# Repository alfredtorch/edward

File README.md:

Edward is an innovative solution that synergizes citizen science with urban farming, utilizing an advanced aquaponic system to address environmental challenges. Edward aims to produce sustainable food sources while fostering community involvement and contributing to a healthier, more sustainable urban environment.

Designed as an expansive urban farming laboratory, Edward initially focuses on aquaponics. This highly efficient farming method is capable of producing local food with minimal resource impact and effort. By transforming existing water bodies, such as ponds or basins, into productive food sources, Edward epitomizes the principles of the circular economy.

Key Features
- Smart Garden Community: Build your self-sufficient technology platform and transform public spaces into urban farming areas.
- Citizen Science: Share information and engage in community-driven research.
- Open Source: Driven by the community, promoting collaboration and innovation.
- Modular Design: Based on the principles of the circular economy, allowing adaptability and scalability.

> ## Software Development Needed
> Please visit the [Software Specification Sheet](SoftwareSpecificationSheetM2.md) if you would like to collaborate and help to develop Edward.
> ## On-Going Documentation
> Different sections in this repository needs to verified. Please feel free to submit corrections, if you would like to collaborate and help to develop Edward.

# Growing Lab & Sharing Knowledge
Edward fosters continuous improvement through community involvement at multiple levels. Individuals manage local stations, benefit from fresh food, and participate in testing new biological scenarios. This approach enriches community knowledge and enhances the numerical model.

The Sustainable Food Cycle and Optimization Biological Cycle are central to Edward's innovative approach. The Sustainable Food Cycle focuses on creating a cradle-to-cradle system where organic waste is transformed into bio converters and natural bio cycles, producing organic food for fish and yielding fresh vegetables. This cycle epitomizes resource efficiency and sustainability. Meanwhile, the Optimization Biological Cycle leverages citizen science and advanced technologies like machine learning and autonomous control to refine and enhance farming practices. Through community-driven research, scenario experimentation, and gamification, this cycle ensures continuous improvement and optimization of the entire system.

## Sharing Knowledge
For individuals, Edward offers a novel way to connect with nature and their community. Members assume shared responsibility for their plants and fish, gaining knowledge and forming new connections, both digitally and in person. This hands-on experience not only yields healthy food but also underlines a Return on Research (RoR) approach, valuing the knowledge gained from community-led research and innovation.

Key Features
* Citizen-Operated Stations: Gather observations for new biological scenarios like light conditions or tidal cycles.
* Mobile App Support: Easy sharing of observations with scientists, encouraging dynamic information exchange.
* Participative and Gamified Approach: Encourages dialogue, sharing through text and images, and collective data contribution.
* AI-Driven Insights: Data from multiple stations feed into AI models for valuable insights into small-scale and industrial agricultural practices, such as pisciculture.

## Research Project 1 : Water Cooled LEDs

Improve the maintenance cost and efficiency with water-cooled LEDs for grow lights. This study focuses on the efficient thermal management of the grow light. Optimal cooling will provide long-term stable light characteristics and increase lifespan. Additionally, the possible waste heat can be used to heat the fish tank.

## Phases
1. **Design Possibilities:** Explore various design possibilities such as heat sinks, LED holders, and more.
2. **Check Safety Concerns:** Address safety concerns including risks of electrocution, fire hazards, and appropriate light levels.
3. **Regulate Water Pump and Light Intensity:** Control the water pump and adjust light intensity based on a state machine and scheduling.
4. **Measure Light Quality:** Assess light quality by measuring energy, wavelengths, and consumption over time.

## Development Project 1 : Move away from Home Assistant

The current prototype system is powered by Home Assistant with ESPHome running on a local Raspberry Pi. This setup was great for quickly prototyping a proof of concept. However, the main challenges faced by the current system are:
- It is not a standalone system (requires both Raspberry Pi and Station Controller).
- There is no option for easy remote monitoring of the system (NAT, DNS, Public IP).
- Missing control options (regular self-calibration, failsafe mode).

<p align="center>
  >
</p>

# Files & Folders
The project is currently mainly organised in this respository.
All shared by Licence... 
## [Hardware](Hardware.md)
## [Hardware PCB Repo](/Hardware/)
## [Components](Components.md)
## [Software YAML Repo](/Software/)
## [Software Devlopement Specification Sheet](SoftwareSpecificationSheetM2.md)
## [Discord Server](https://discord.gg/AFunXj2wjE)
## [HackADay.io Project](https://hackaday.io/project/197025-edwardfarm)

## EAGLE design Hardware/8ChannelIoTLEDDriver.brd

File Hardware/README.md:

| Filename | Notes |
| --- | --- |
FishTankControllerV2 | Control the Greenhouse & Fish Tank with safe DC motors |
GreenHouseControllerV2 | Control the Greenhouse & Fish Tank with with powerful AC motors |
IoTSSensorBoardV2 | Measure Heatsink Temperature LM75B or TMP1075 |
PowerMosfetGSVINRailV1 | Control 4 DC Load Module with GreenHouseControllerV2 |
PowerMosfetsSGVINRailV1 | Control 4 DC Load Modulel Module with GreenHouseControllerV2 |
Relay4ChannelBoard | Control 230V Relay 4Channel Module with GreenHouseControllerV2 |
SSR4ChannelBoard | Control 230V SSR 4Channel Module with GreenHouseControllerV2 |

<p align="center">

<br>
8 Channel Rebel - 8ChannelRebelSSR_v5
<br>

<br>
Helios - 8ChannelIoTLEDDriver
<br>

<br>
Green House - GreenHouseControllerV2
<br>

<br>
FishTankControllerV2
<br>

<br>
Relay4ChannelBoard - Control 230V Relay 4Channel Module with Green-House
<br>

<br>
SSR4ChannelBoard - Control 230V SSR 4Channel Module with Green-House
<br>

<br>
PowerMosfetGSVINRailV1
<br>

PowerMosfetSGVINRailV1
<br>
</p>

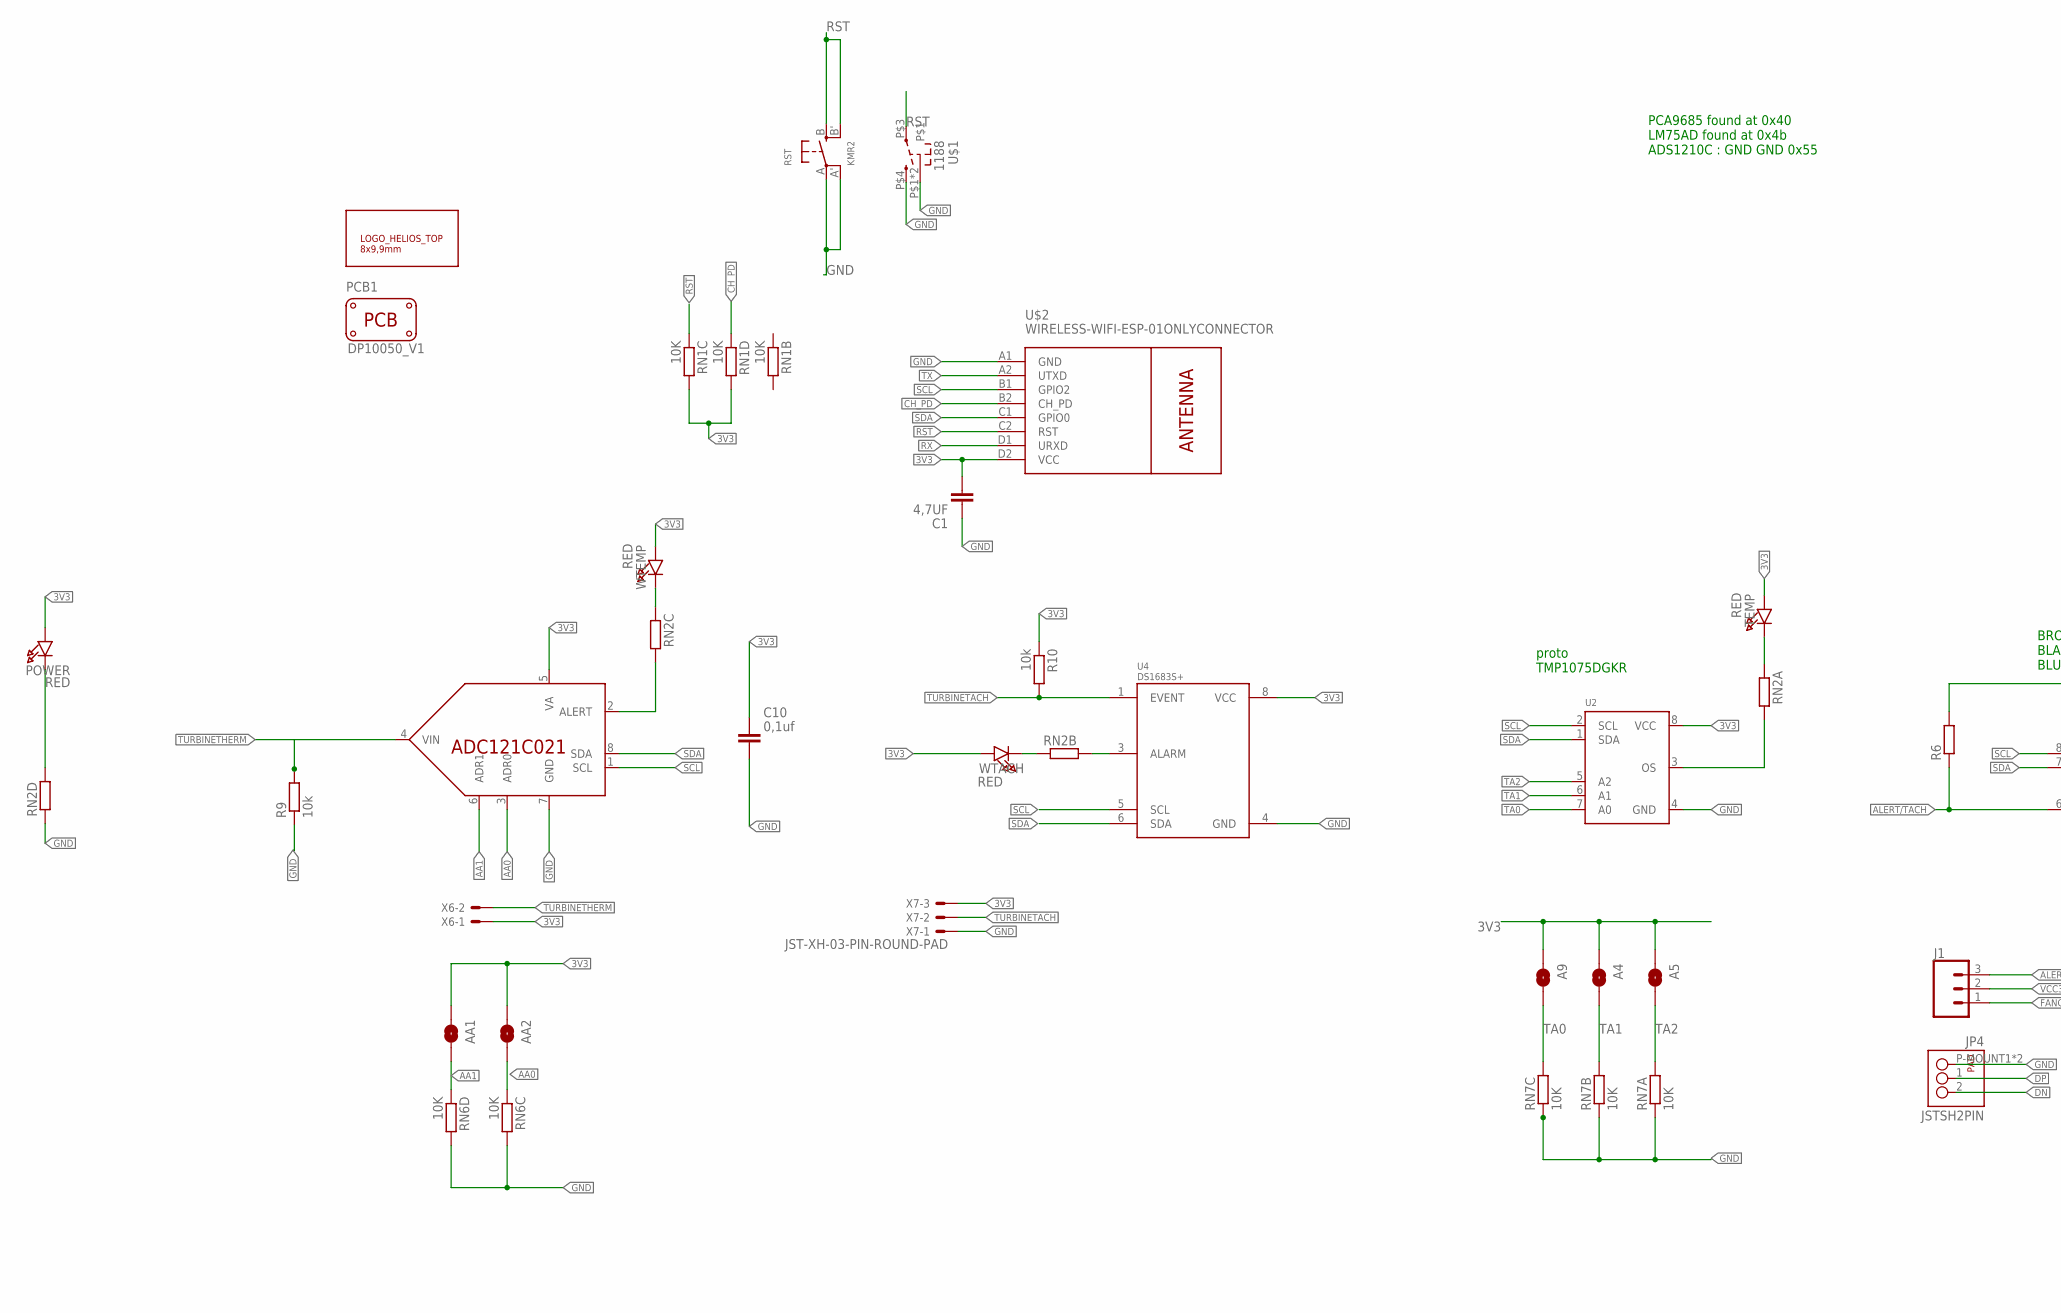
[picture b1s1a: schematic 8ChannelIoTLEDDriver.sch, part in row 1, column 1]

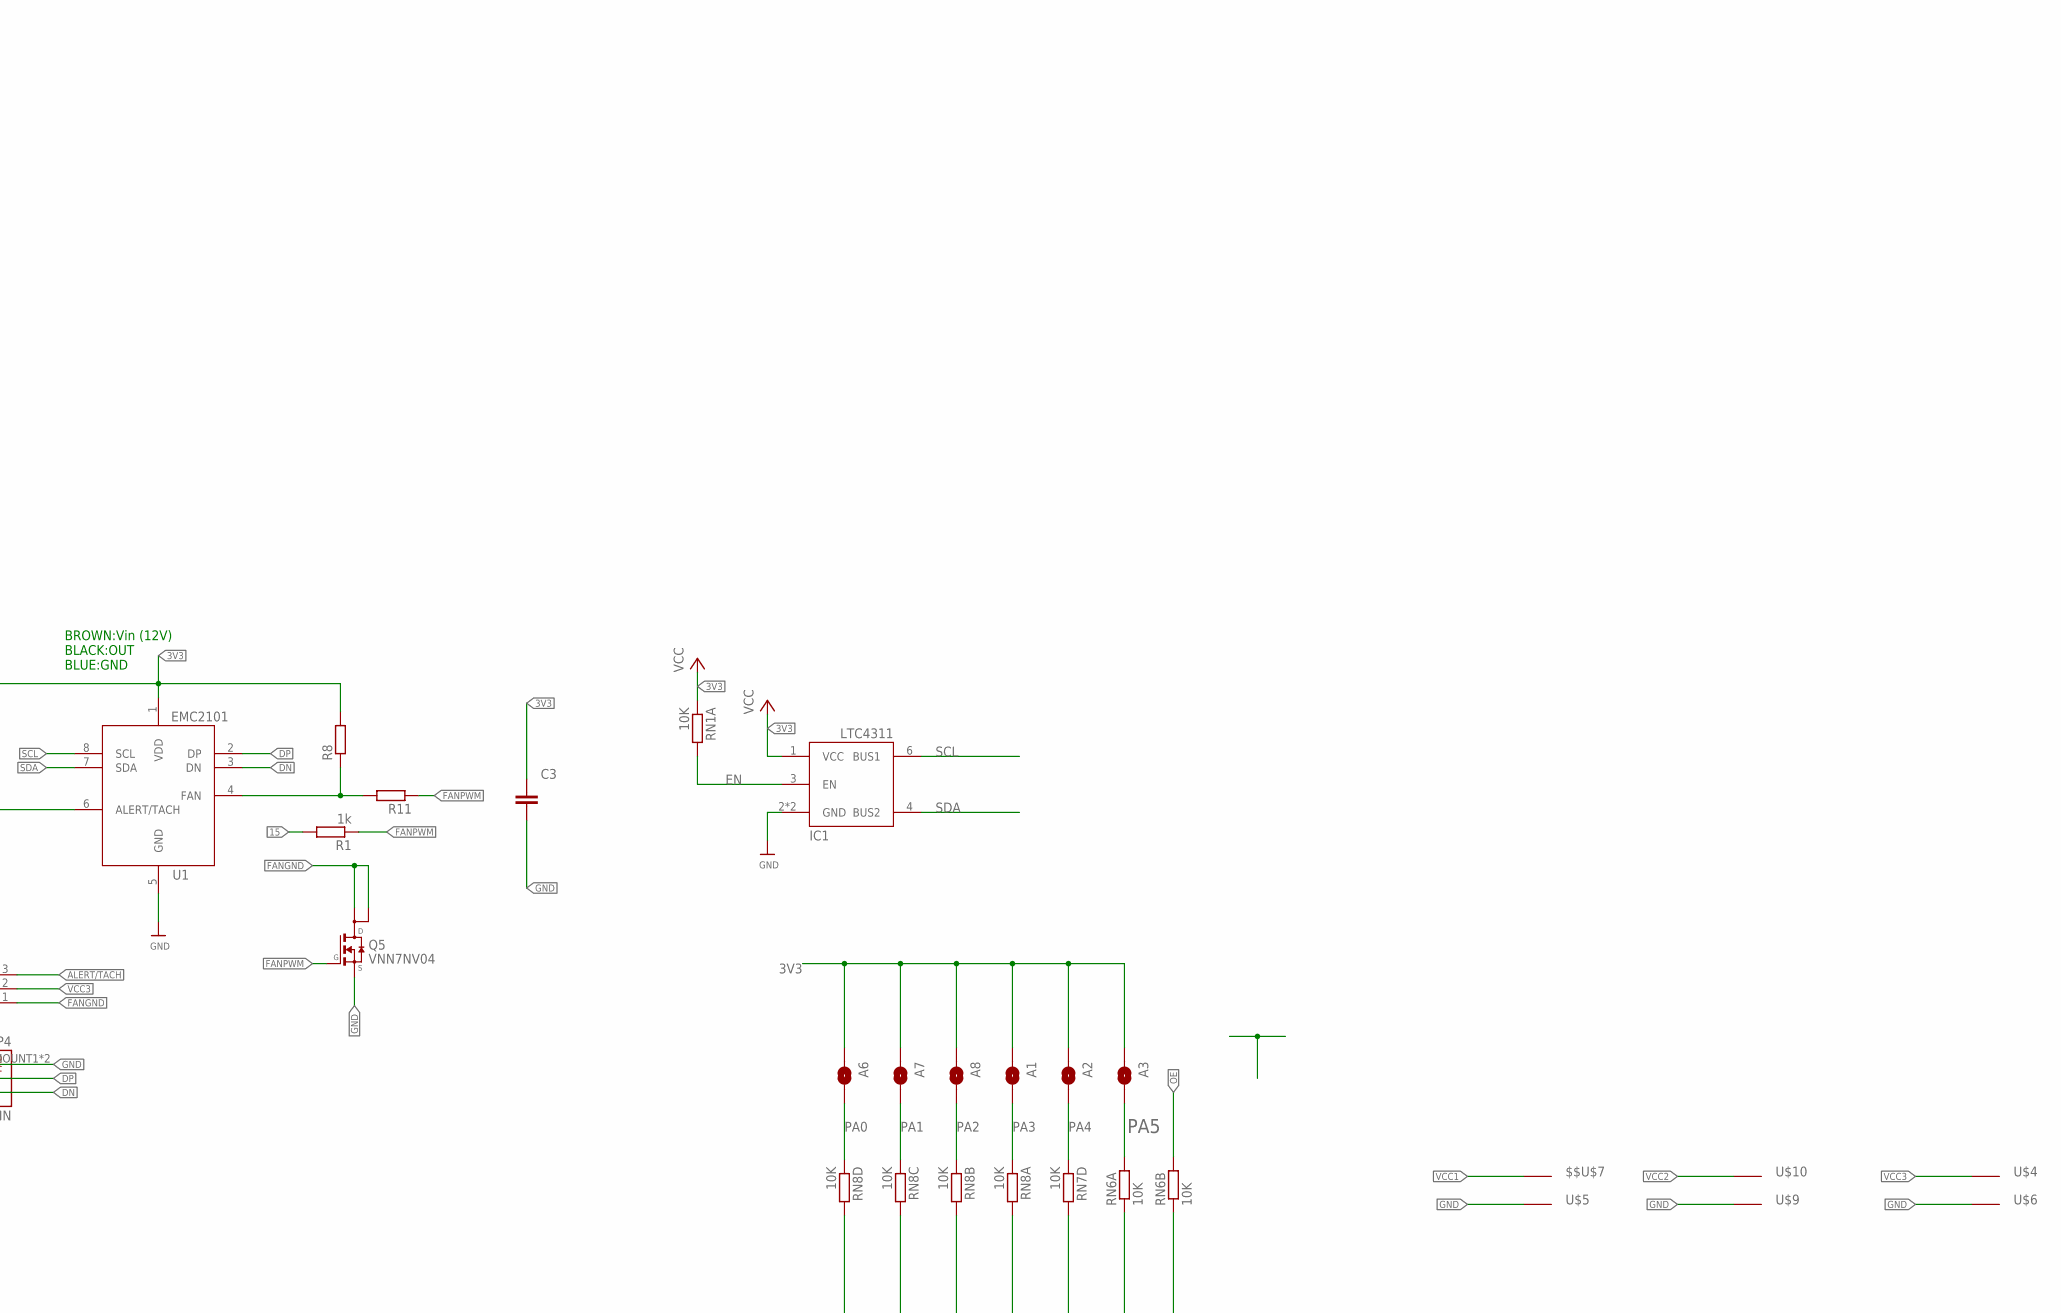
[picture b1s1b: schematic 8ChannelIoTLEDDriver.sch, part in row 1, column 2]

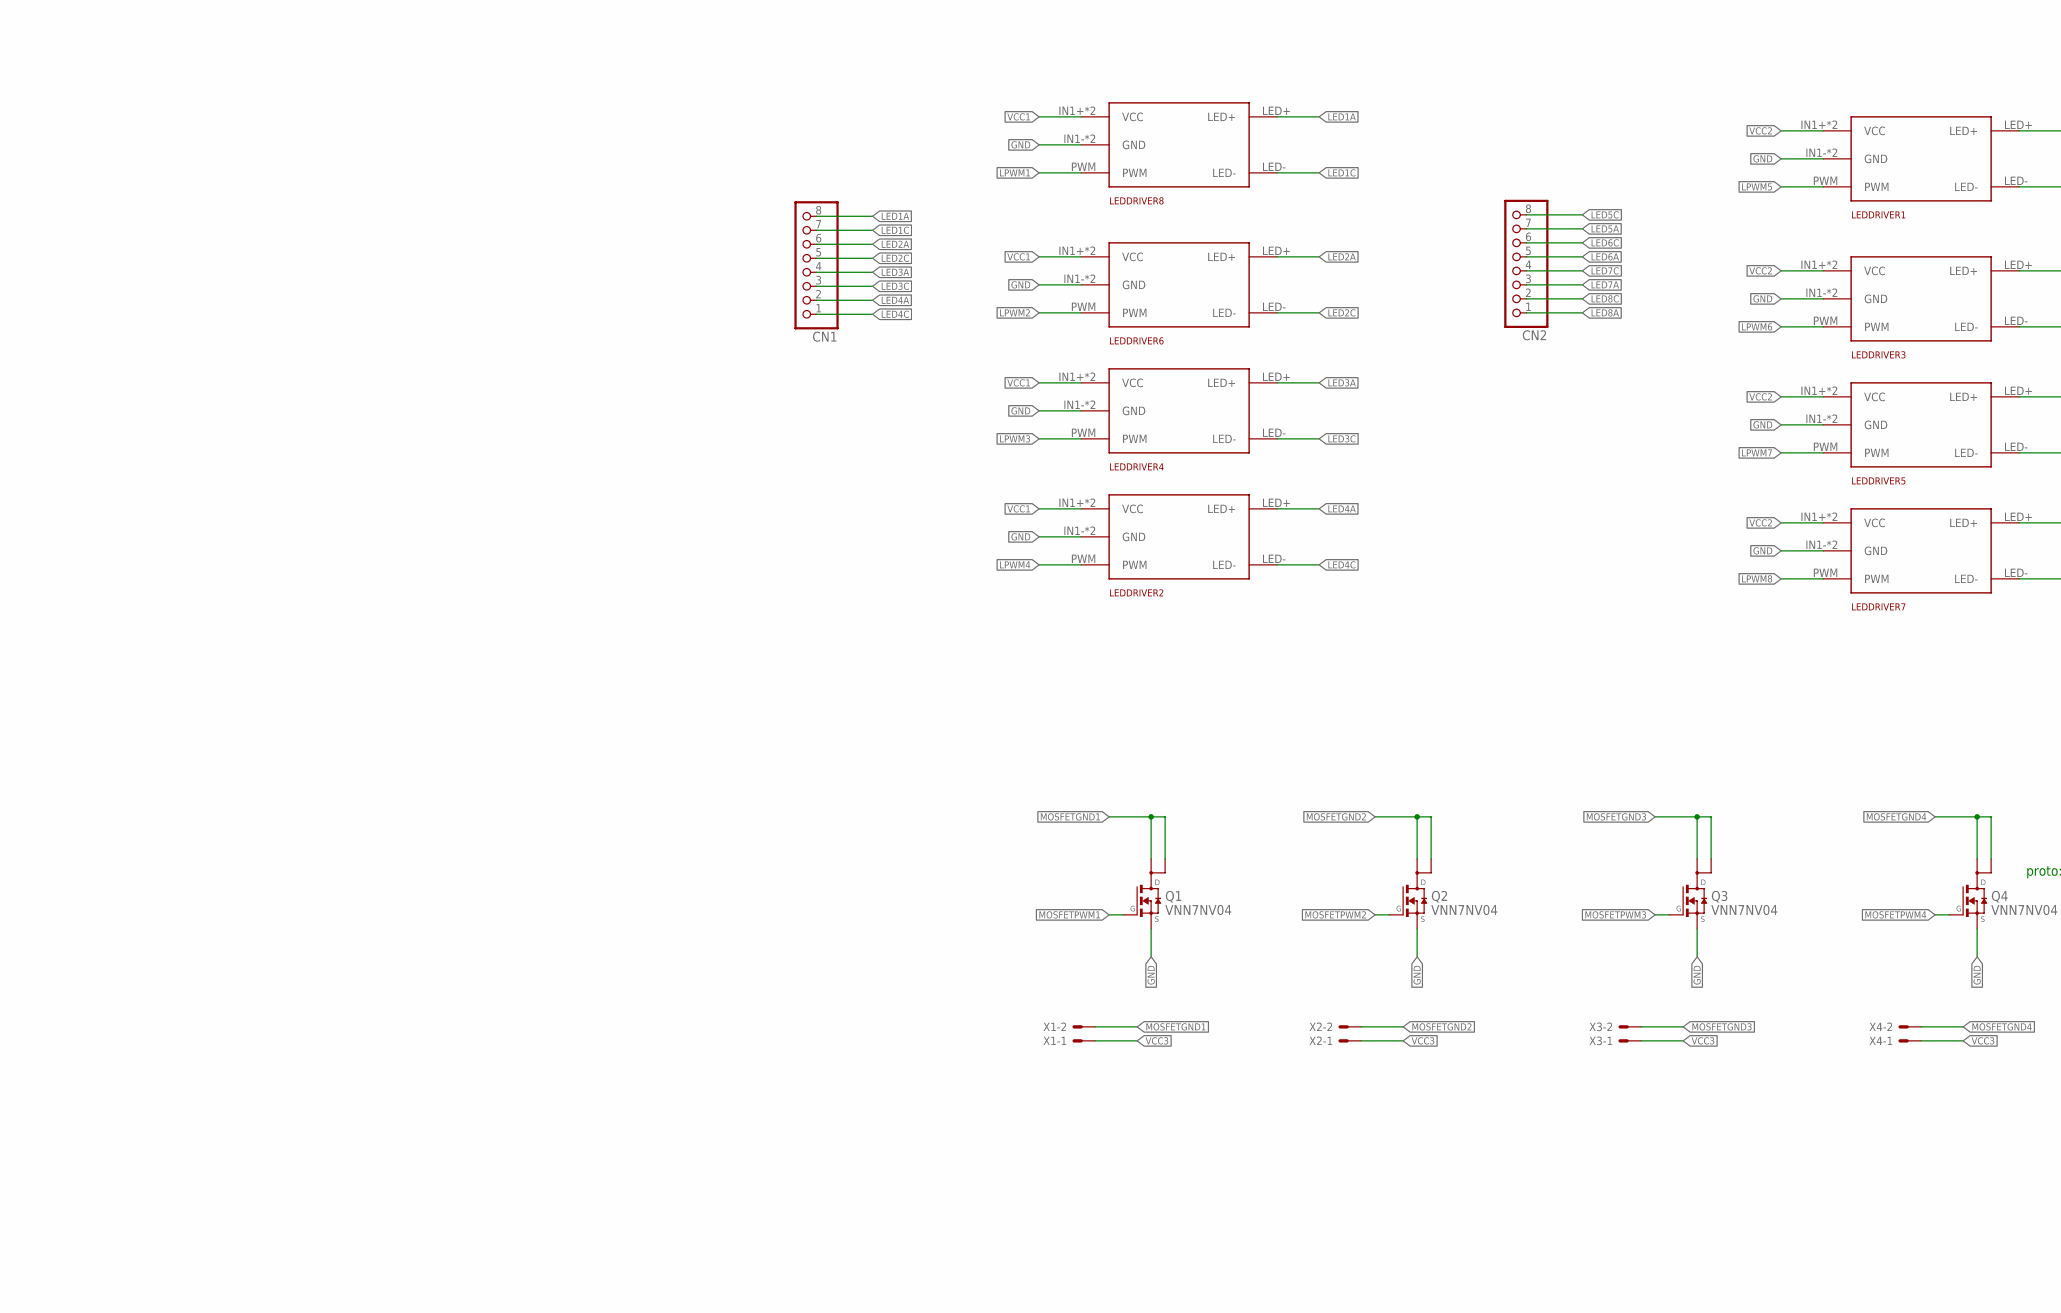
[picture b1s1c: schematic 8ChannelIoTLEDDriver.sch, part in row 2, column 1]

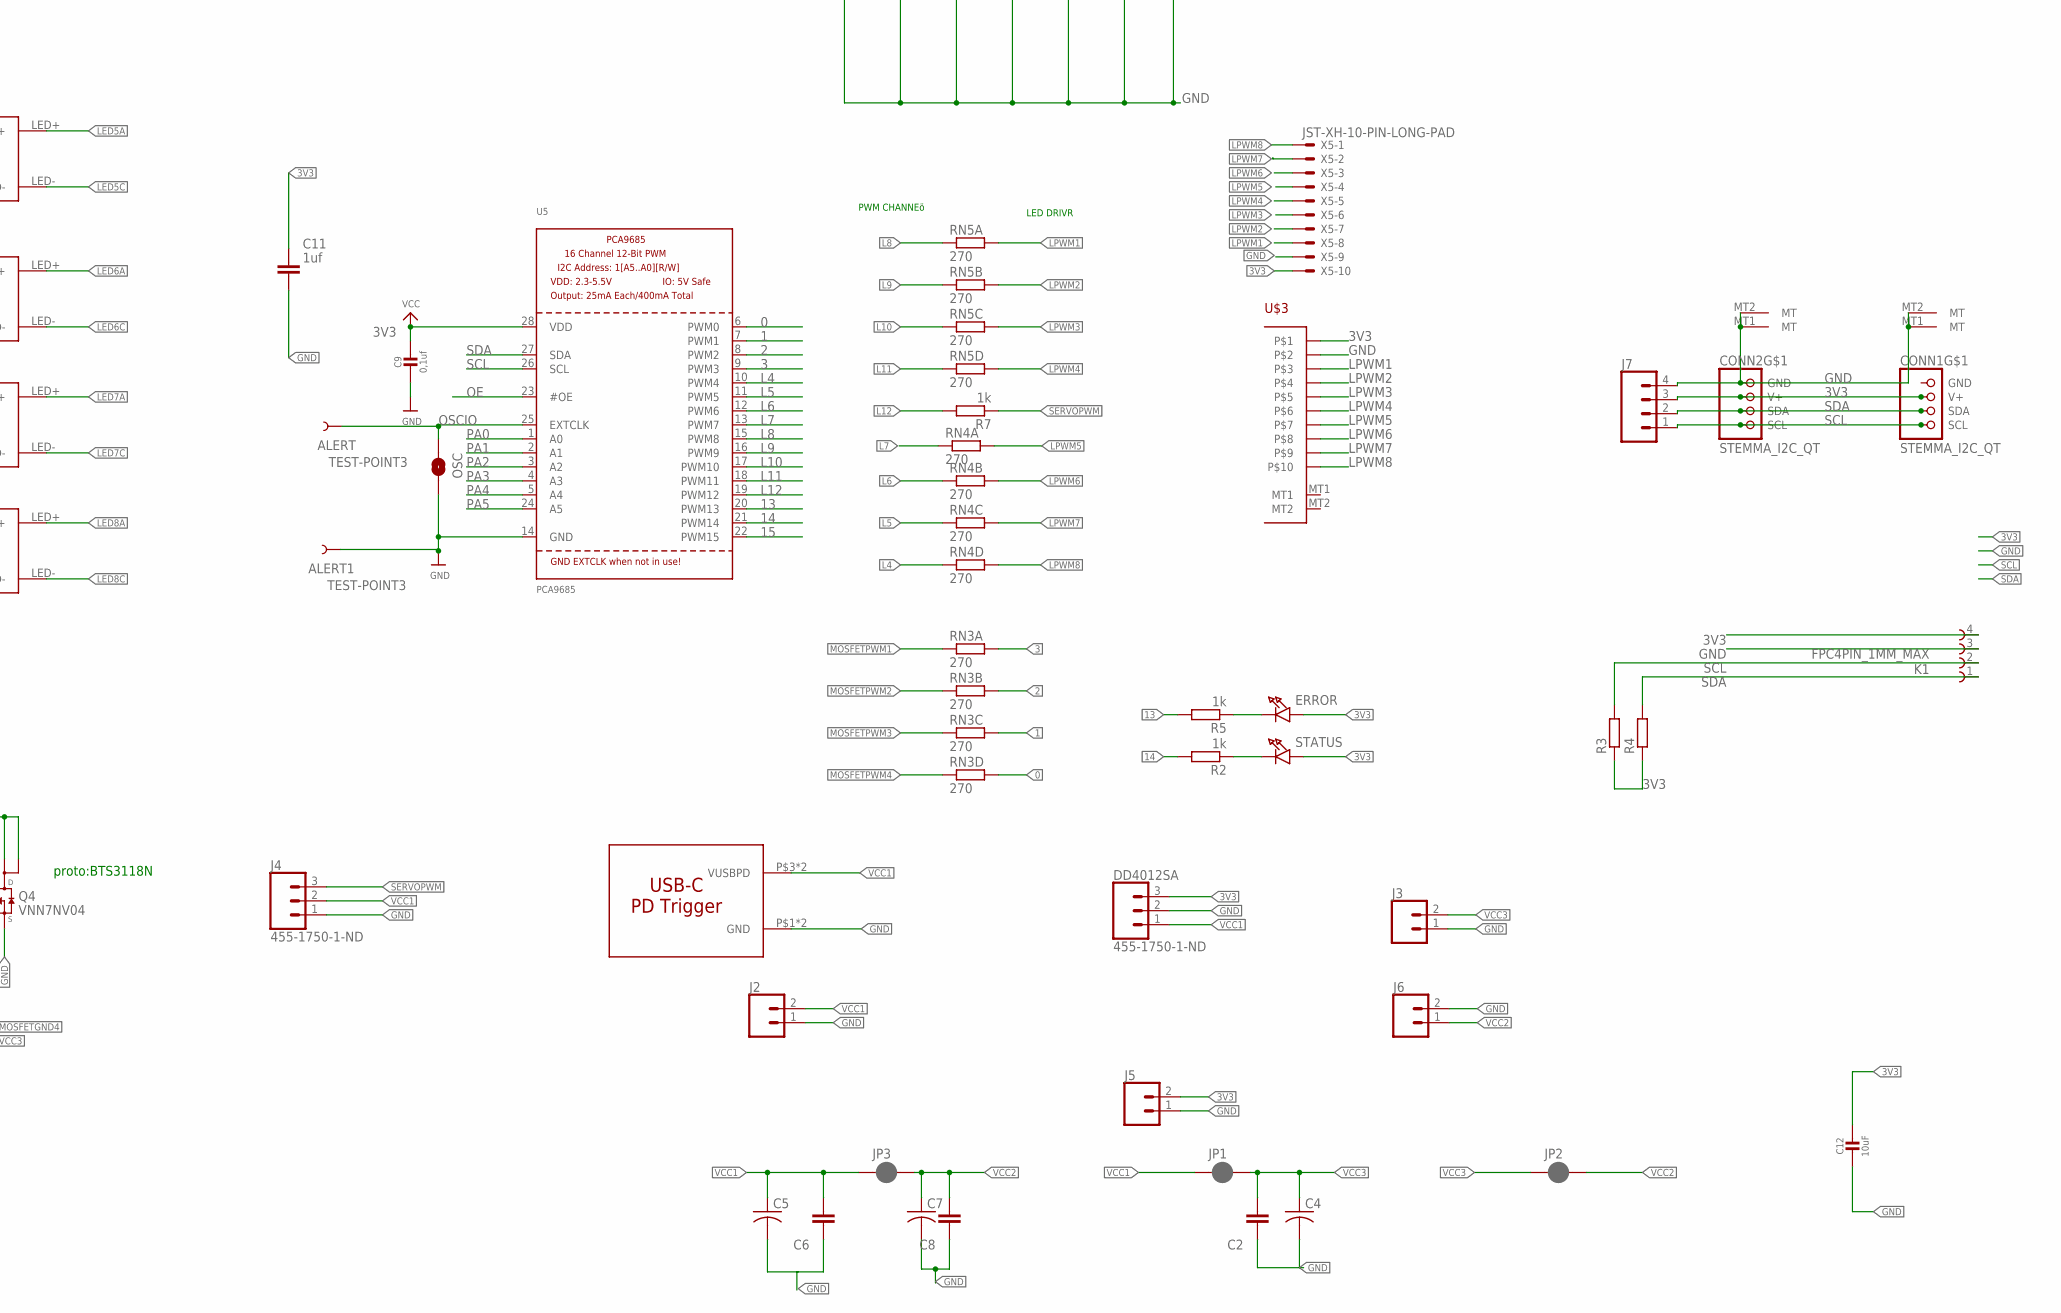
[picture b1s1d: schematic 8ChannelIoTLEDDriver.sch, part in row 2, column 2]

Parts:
$$U$7: TESTHOOK
A1, A2, A3, A4, A5, A6, A7, A8, A9: JUMPER-SMT_2_NO_SILK; SMT-JUMPER_2_NO_SILK
AA1, AA2: JUMPER-SMT_2_NO_SILK; SMT-JUMPER_2_NO_SILK
ALERT, ALERT1: TEST-POINT3; PAD.03X.03
C1: 4,7UF; C805
C2, C3, C6, C8: CAPACITOR_NPOL-0805; C805
C4, C5, C7: C-USC1210; C1210
C9: 0,1uf; 0805-NO
C10: 0,1uf; C805
C11: 1uf; C805
C12: 10uF; 0805-NO
CN1, CN2: JST_8PIN; JSTPH8
CONN1, CONN2: STEMMA_I2C_QT; JST_SH4
DD4012SA: 455-1750-1-ND; 1X03
ERROR: RED; CHIPLED_0805
IC1: LTC4311_SC70; SC70-6L
J1: CONN_03POLAR; MOLEX-1X3
J2, J3, J5: CONN_02POLAR; MOLEX-1X2
J4: 455-1750-1-ND; 1X03
J6: CONN_023.5MM; SCREWTERMINAL-3.5MM-2
J7: CONN_04JST-PH-4-1.0MM; JST-4-SMD-VERT-1.0MM
JP1, JP2, JP3: JUMPER-SMT_2_NC_PASTE_SILK; SMT-JUMPER_2_NC_PASTE_SILK
JP4: JSTSH2PIN; SM02B-SRSS-TB
K1: FPC4PIN_1MM_MAX; FPC_CONN_DOC_4PIN_ENLARGED
LEDDRIVER1, LEDDRIVER2, LEDDRIVER3, LEDDRIVER4, LEDDRIVER5, LEDDRIVER6, LEDDRIVER7, LEDDRIVER8: LEDDRIVERPT4115LONG; 7PINLONGLEDDRIVER
OSC: JUMPER-SMT_2_NO_SILK; SMT-JUMPER_2_NO_SILK
PCB1: PCB_DP_RECTANGLE-50X100; DP10050_V1
POWER: RED; CHIPLED_0805
Q1, Q2, Q3, Q4, Q5: VNN7NV04; SOT223
R1, R2, R5, R7: 1k; R805
R3, R4, R6, R8, R11: RESISTORR805-0805; R805
R9, R10: 10k; R805
RN1, RN6, RN7, RN8: 10K; RN8P-4R-CRA06S
RN2: RESISTOR_ARRAY_4; RN8P-4R-CRA06S
RN3, RN4, RN5: 270; RN8P-4R-CRA06S
RST: KMR2; BTN_KMR2_4.6X2.8
STATUS: RED; CHIPLED_0805
TEMP: RED; CHIPLED_0805
U1: EMC2101-AZCL; MSOP8_0.65MM
U2: TEMP_LM75B; TSSOP8
U3: ADC121C021; MSOP08
U4: DS1683S+; SOIC8-N_MC
U5: PCA9685; TSSOP28
U$1: 1188
U$2: WIRELESS-WIFI-ESP-01ONLYCONNECTOR; WIRELESS-WIFI-ESP-01-ONLYBOTTOM
U$3: FPC-1.0X10; FPC_1.0X10
U$4, U$5, U$6, U$9, U$10: TESTHOOK
U$8: USB_PD_TRIGGER; USB-PDTRIGGER
U$11: LOGOTOPHELIOS
WTACH: RED; CHIPLED_0805
WTEMP: RED; CHIPLED_0805
X1, X2, X3, X4, X6: JST-XH-02-PIN-ROUND-PAD; JST-XH-02-PACKAGE-ROUND-PAD
X5: JST-XH-10-PIN-LONG-PAD; JST-XH-10-PACKAGE-LONG-PAD
X7: JST-XH-03-PIN-ROUND-PAD; JST-XH-03-PACKAGE-ROUND-PAD

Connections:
0: RN3.5 (2), U5.6 (PWM0)
1: RN3.6 (2), U5.7 (PWM1)
2: RN3.7 (2), U5.8 (PWM2)
3: RN3.8 (2), U5.9 (PWM3)
3V3: A1.1, A2.1, A3.1, A4.1, A5.1, A6.1, A7.1, A8.1, A9.1, AA1.1, AA2.1, C1.2, C3.1, C9.1, C10.1, C11.1, C12.1, CONN1.2 (V+), CONN2.2 (V+), DD4012SA.3, ERROR.A, IC1.1 (VCC), J5.2, J7.3, K1.4, POWER.A, R3.1, R4.1, R6.2, R8.2, R10.1, RN1.1, RN1.5 (2), RN1.6 (2), STATUS.A, TEMP.A, U1.1 (VDD), U2.8 (VCC), U3.5 (VA), U4.8 (VCC), U5.28 (VDD), U$2.D2 (VCC), U$3.1, WTACH.A, WTEMP.A, X5.10, X6.1, X7.3
13: R5.2, U5.20 (PWM13)
14: R2.2, U5.21 (PWM14)
15: R1.2, U5.22 (PWM15)
AA0: AA2.2, RN6.3 (1), U3.3 (ADR0)
AA1: AA1.2, RN6.4 (1), U3.6 (ADR1)
ALARM1: RN2.6 (2), U3.2 (ALERT)
ALARM2: RN2.8 (2), U2.3 (OS)
ALERT/TACH: J1.3, R6.1, U1.6 (ALERT/TACH)
CH_PD: RN1.4 (1), U$2.B2 (CH_PD)
DN: JP4.2, U1.3 (DN)
DP: JP4.1, U1.2 (DP)
EN: IC1.3 (EN), RN1.8 (2)
FANGND: J1.1, Q5.2 (D), Q5.4 (D2)
FANPWM: Q5.1 (G), R1.1, R11.1
GND: ALERT1.P$1, C1.1, C2.1, C3.2, C4.2, C5.2, C6.1, C7.2, C8.1, C9.2, C10.2, C11.2, C12.2, CONN1.MT1 (MT), CONN1.MT2 (MT), CONN2.1 (GND), CONN2.MT1 (MT), CONN2.MT2 (MT), DD4012SA.2, IC1.2 (GND), IC1.5 (GND), J2.1, J3.1, J4.1, J5.1, J6.2, J7.4, JP4.P-MOUNT1, JP4.P-MOUNT2, K1.3, LEDDRIVER1.IN1- (GND), LEDDRIVER1.IN2- (GND), LEDDRIVER2.IN1- (GND), LEDDRIVER2.IN2- (GND), LEDDRIVER3.IN1- (GND), LEDDRIVER3.IN2- (GND), LEDDRIVER4.IN1- (GND), LEDDRIVER4.IN2- (GND), LEDDRIVER5.IN1- (GND), LEDDRIVER5.IN2- (GND), LEDDRIVER6.IN1- (GND), LEDDRIVER6.IN2- (GND), LEDDRIVER7.IN1- (GND), LEDDRIVER7.IN2- (GND), LEDDRIVER8.IN1- (GND), LEDDRIVER8.IN2- (GND), OSC.2, Q1.3 (S), Q2.3 (S), Q3.3 (S), Q4.3 (S), Q5.3 (S), R9.1, RN2.4 (1), RN6.1, RN6.2 (1), RN6.5 (2), RN6.6 (2), RN7.1, RN7.2 (1), RN7.3 (1), RN7.5 (2), RN8.5 (2), RN8.6 (2), RN8.7 (2), RN8.8 (2), RST.A, RST.A' (P1), U1.5 (GND), U2.4 (GND), U3.7 (GND), U4.4 (GND), U5.14 (GND), U$1.P$1, U$1.P$2, U$1.P$4 (3), U$2.A1 (GND), U$3.2, U$5.P$1, U$6.P$1, U$8.P$1 (GND), U$8.P$2 (GND), U$9.P$1, X5.9, X7.1
L4: RN4.4 (1), U5.10 (PWM4)
L5: RN4.3 (1), U5.11 (PWM5)
L6: RN4.2 (1), U5.12 (PWM6)
L7: RN4.1, U5.13 (PWM7)
L8: RN5.1, U5.15 (PWM8)
L9: RN5.2 (1), U5.16 (PWM9)
L10: RN5.3 (1), U5.17 (PWM10)
L11: RN5.4 (1), U5.18 (PWM11)
L12: R7.2, U5.19 (PWM12)
LED1A: CN1.8, LEDDRIVER8.LED+
LED1C: CN1.7, LEDDRIVER8.LED-
LED2A: CN1.6, LEDDRIVER6.LED+
LED2C: CN1.5, LEDDRIVER6.LED-
LED3A: CN1.4, LEDDRIVER4.LED+
LED3C: CN1.3, LEDDRIVER4.LED-
LED4A: CN1.2, LEDDRIVER2.LED+
LED4C: CN1.1, LEDDRIVER2.LED-
LED5A: CN2.7, LEDDRIVER1.LED+
LED5C: CN2.8, LEDDRIVER1.LED-
LED6A: CN2.5, LEDDRIVER3.LED+
LED6C: CN2.6, LEDDRIVER3.LED-
LED7A: CN2.3, LEDDRIVER5.LED+
LED7C: CN2.4, LEDDRIVER5.LED-
LED8A: CN2.1, LEDDRIVER7.LED+
LED8C: CN2.2, LEDDRIVER7.LED-
LPWM1: LEDDRIVER8.PWM, RN5.8 (2), U$3.3, X5.8
LPWM2: LEDDRIVER6.PWM, RN5.7 (2), U$3.4, X5.7
LPWM3: LEDDRIVER4.PWM, RN5.6 (2), U$3.5, X5.6
LPWM4: LEDDRIVER2.PWM, RN5.5 (2), U$3.6, X5.5
LPWM5: LEDDRIVER1.PWM, RN4.8 (2), U$3.7, X5.4
LPWM6: LEDDRIVER3.PWM, RN4.7 (2), U$3.8, X5.3
LPWM7: LEDDRIVER5.PWM, RN4.6 (2), U$3.9, X5.2
LPWM8: LEDDRIVER7.PWM, RN4.5 (2), U$3.10, X5.1
MOSFETGND1: Q1.2 (D), Q1.4 (D2), X1.2
MOSFETGND2: Q2.2 (D), Q2.4 (D2), X2.2
MOSFETGND3: Q3.2 (D), Q3.4 (D2), X3.2
MOSFETGND4: Q4.2 (D), Q4.4 (D2), X4.2
MOSFETPWM1: Q1.1 (G), RN3.1
MOSFETPWM2: Q2.1 (G), RN3.2 (1)
MOSFETPWM3: Q3.1 (G), RN3.3 (1)
MOSFETPWM4: Q4.1 (G), RN3.4 (1)
unnamed: RN2.1, TEMP.C
unnamed: RN2.2 (1), WTACH.C
unnamed: RN2.3 (1), WTEMP.C
unnamed: RN2.7 (2), U4.3 (ALARM)
unnamed: POWER.C, RN2.5 (2)
unnamed: R8.1, R11.2, U1.4 (FAN)
unnamed: R2.1, STATUS.C
unnamed: ERROR.C, R5.1
OE: RN6.7 (2), U5.23 (#OE)
OSCIO: ALERT.P$1, OSC.1, U5.25 (EXTCLK)
PA0: A6.2, RN8.4 (1), U5.1 (A0)
PA1: A7.2, RN8.3 (1), U5.2 (A1)
PA2: A8.2, RN8.2 (1), U5.3 (A2)
PA3: A1.2, RN8.1, U5.4 (A3)
PA4: A2.2, RN7.4 (1), U5.5 (A4)
PA5: A3.2, RN6.8 (2), U5.24 (A5)
RST: RN1.3 (1), RST.B (S), RST.B' (S1), U$1.P$3 (1), U$2.C2 (RST)
RX: U$2.D1 (URXD)
SCL: CONN1.4 (SCL), CONN2.4 (SCL), IC1.6 (BUS1), J7.1, K1.2, R3.2, U1.8 (SCL), U2.2 (SCL), U3.1 (SCL), U4.5 (SCL), U5.26 (SCL), U$2.B1 (GPIO2)
SDA: CONN1.3 (SDA), CONN2.3 (SDA), IC1.4 (BUS2), J7.2, K1.1, R4.2, U1.7 (SDA), U2.1 (SDA), U3.8 (SDA), U4.6 (SDA), U5.27 (SDA), U$2.C1 (GPIO0)
SERVOPWM: J4.3, R7.1
TA0: A9.2, RN7.6 (2), U2.7 (A0)
TA1: A4.2, RN7.7 (2), U2.6 (A1)
TA2: A5.2, RN7.8 (2), U2.5 (A2)
TURBINETACH: R10.2, U4.1 (EVENT), X7.2
TURBINETHERM: R9.2, U3.4 (VIN), X6.2
TX: U$2.A2 (UTXD)
VCC1: $$U$7.P$1, C5.1, C6.2, DD4012SA.1, J2.2, J4.2, JP1.1, JP3.1, LEDDRIVER2.IN1+ (VCC), LEDDRIVER2.IN2+ (VCC), LEDDRIVER4.IN1+ (VCC), LEDDRIVER4.IN2+ (VCC), LEDDRIVER6.IN1+ (VCC), LEDDRIVER6.IN2+ (VCC), LEDDRIVER8.IN1+ (VCC), LEDDRIVER8.IN2+ (VCC), U$8.P$3 (VUSBPD), U$8.P$4 (VUSBPD)
VCC2: C7.1, C8.2, J6.1, JP2.2, JP3.2, LEDDRIVER1.IN1+ (VCC), LEDDRIVER1.IN2+ (VCC), LEDDRIVER3.IN1+ (VCC), LEDDRIVER3.IN2+ (VCC), LEDDRIVER5.IN1+ (VCC), LEDDRIVER5.IN2+ (VCC), LEDDRIVER7.IN1+ (VCC), LEDDRIVER7.IN2+ (VCC), U$10.P$1
VCC3: C2.2, C4.1, J1.2, J3.2, JP1.2, JP2.1, U$4.P$1, X1.1, X2.1, X3.1, X4.1

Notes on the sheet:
BROWN:Vin (12V) BLACK:OUT BLUE:GND
PCA9685 found at 0x40 LM75AD found at 0x4b ADS1210C : GND GND 0x55
LED DRIVR
PWM CHANNEö
proto:BTS3118N
proto TMP1075DGKR

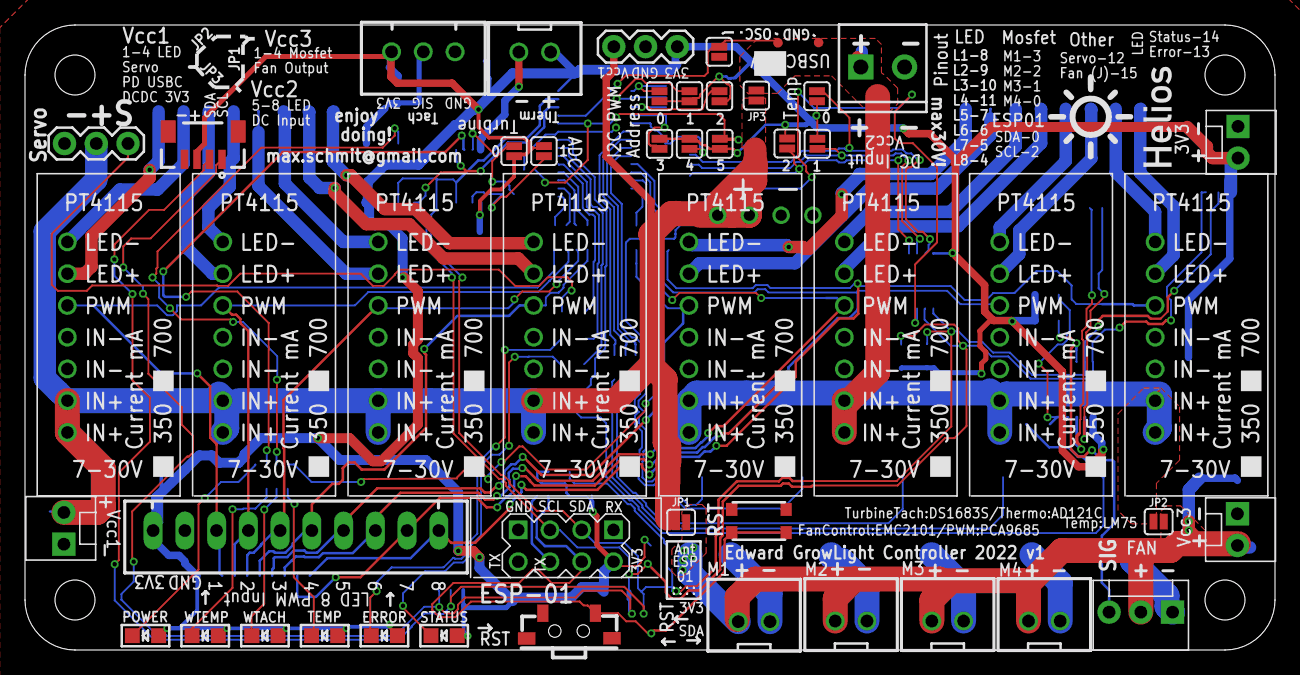
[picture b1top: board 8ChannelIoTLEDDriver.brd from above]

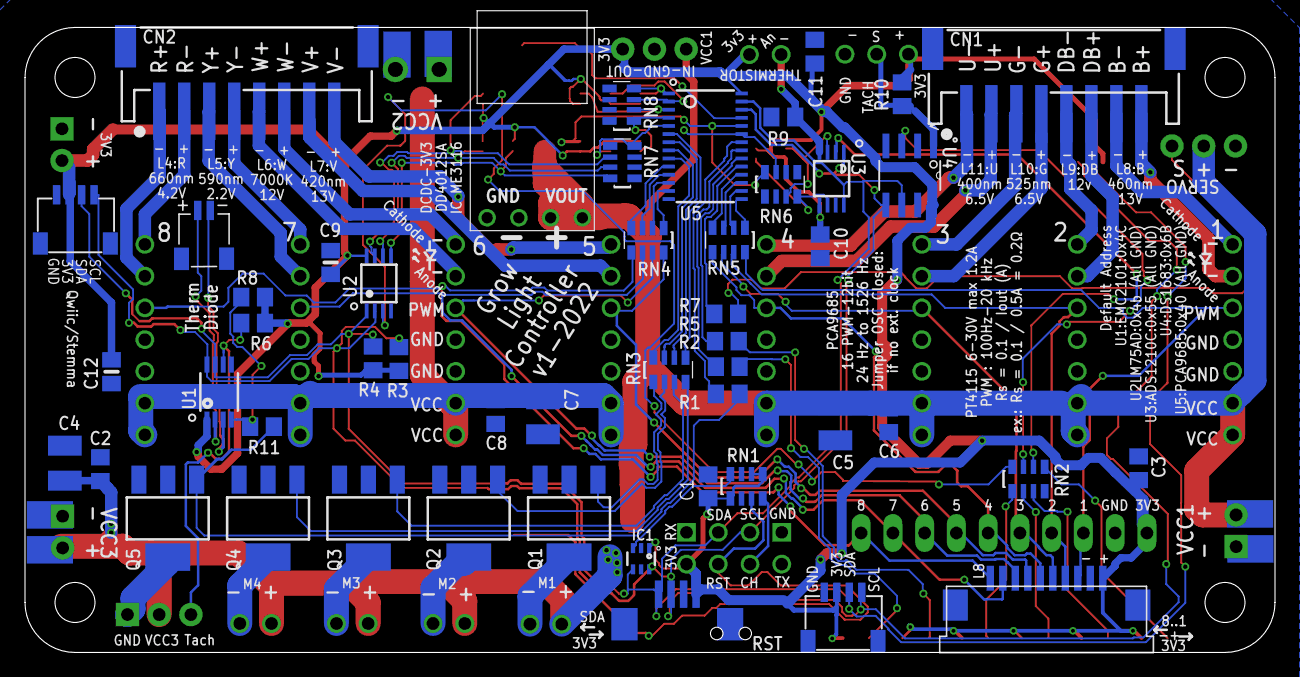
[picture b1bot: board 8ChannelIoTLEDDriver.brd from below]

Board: 2 copper layers, 100.0 x 50.0 mm, 107 parts (56 on the bottom side), 89 nets.

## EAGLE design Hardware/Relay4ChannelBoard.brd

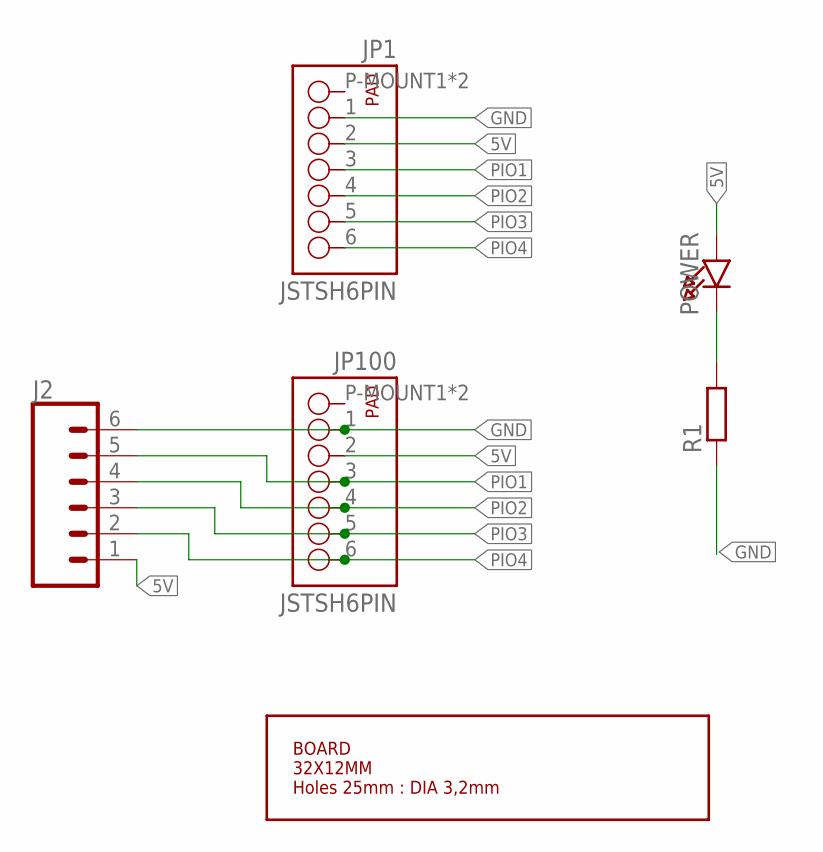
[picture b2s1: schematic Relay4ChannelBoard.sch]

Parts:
J2: CONN_06SILK_FEMALE_PTH; 1X06
JP1, JP100: JSTSH6PIN; SM06B-SRSS-TB
POWER: RED; CHIPLED_0805
R1: RESISTORR805-0805; R805
U$1: BOARD32X12; OVAL3212MM

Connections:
5V: J2.1, JP1.2, JP100.2, POWER.A
GND: J2.6, JP1.1, JP100.1, R1.1
unnamed: POWER.C, R1.2
PIO1: J2.5, JP1.3, JP100.3
PIO2: J2.4, JP1.4, JP100.4
PIO3: J2.3, JP1.5, JP100.5
PIO4: J2.2, JP1.6, JP100.6

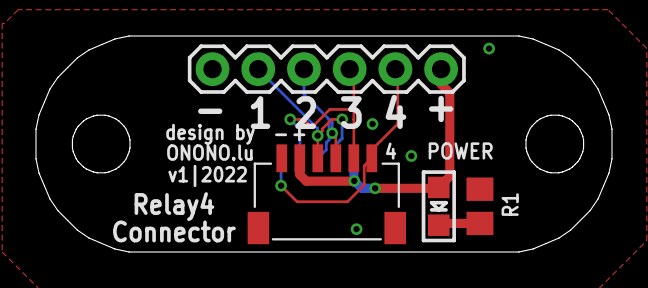
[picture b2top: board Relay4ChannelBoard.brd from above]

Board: 2 copper layers, 32.0 x 12.0 mm, 6 parts (1 on the bottom side), 7 nets.

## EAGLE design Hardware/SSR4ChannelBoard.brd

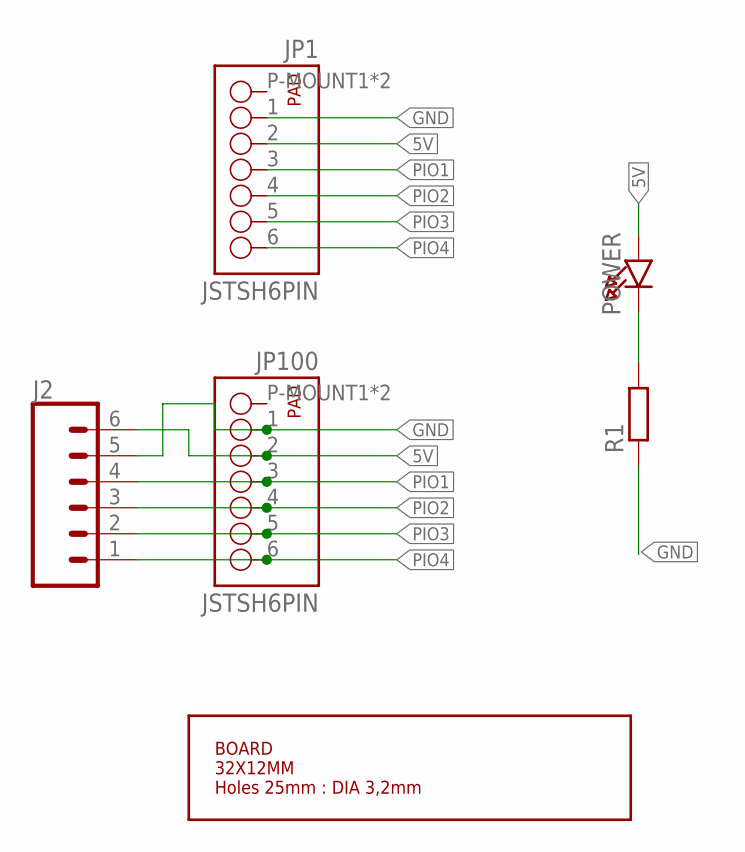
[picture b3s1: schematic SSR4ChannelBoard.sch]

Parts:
J2: CONN_06SILK_FEMALE_PTH; 1X06
JP1, JP100: JSTSH6PIN; SM06B-SRSS-TB
POWER: RED; CHIPLED_0805
R1: RESISTORR805-0805; R805
U$1: BOARD32X12; OVAL3212MM

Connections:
5V: J2.6, JP1.2, JP100.2, POWER.A
GND: J2.5, JP1.1, JP100.1, R1.1
unnamed: POWER.C, R1.2
PIO1: J2.4, JP1.3, JP100.3
PIO2: J2.3, JP1.4, JP100.4
PIO3: J2.2, JP1.5, JP100.5
PIO4: J2.1, JP1.6, JP100.6

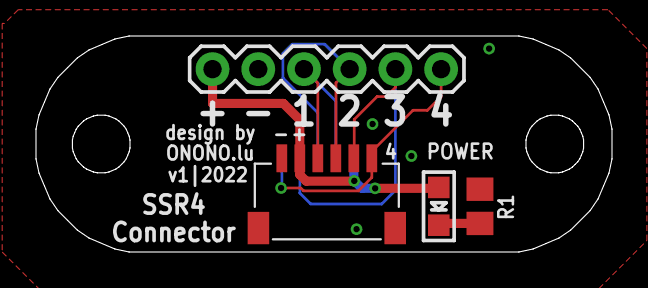
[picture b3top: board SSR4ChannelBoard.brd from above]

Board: 2 copper layers, 32.0 x 12.0 mm, 6 parts (1 on the bottom side), 7 nets.

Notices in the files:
parts and their libraries:
microbuilder: This work is placed in the public domain, and may be freely used for commercial and non-commercial work with the following conditions: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
SparkFun-Connectors: Licensing: Creative Commons ShareAlike 4.0 International - https://creativecommons.org/licenses/by-sa/4.0
